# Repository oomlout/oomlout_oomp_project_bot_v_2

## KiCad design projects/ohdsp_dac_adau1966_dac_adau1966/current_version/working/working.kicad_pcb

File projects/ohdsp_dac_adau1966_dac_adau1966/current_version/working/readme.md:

# dac_adau1966
 
## summary 
* id: ohdsp_dac_adau1966_dac_adau1966
* user: ohdsp
* name: dac_adau1966
* board: dac_adau1966
* repo: https://github.com/ohdsp/DAC-ADAU1966
* src_file_repo_kicad_pcb: KiCad/DAC-ADAU1966.kicad_pcb
* src_file_repo_kicad_pcb_link: https://github.com/ohdsp/DAC-ADAU1966/tree/master/KiCad/DAC-ADAU1966.kicad_pcb

* src_file_repo_sch: 
* src_file_repo_sch_link: https://github.com/ohdsp/DAC-ADAU1966/tree/master/
* full details link: https://github.com/oomlout/oomlout_oomp_project_bot_v_2/tree/main/projects/ohdsp_dac_adau1966_dac_adau1966/current_version/working

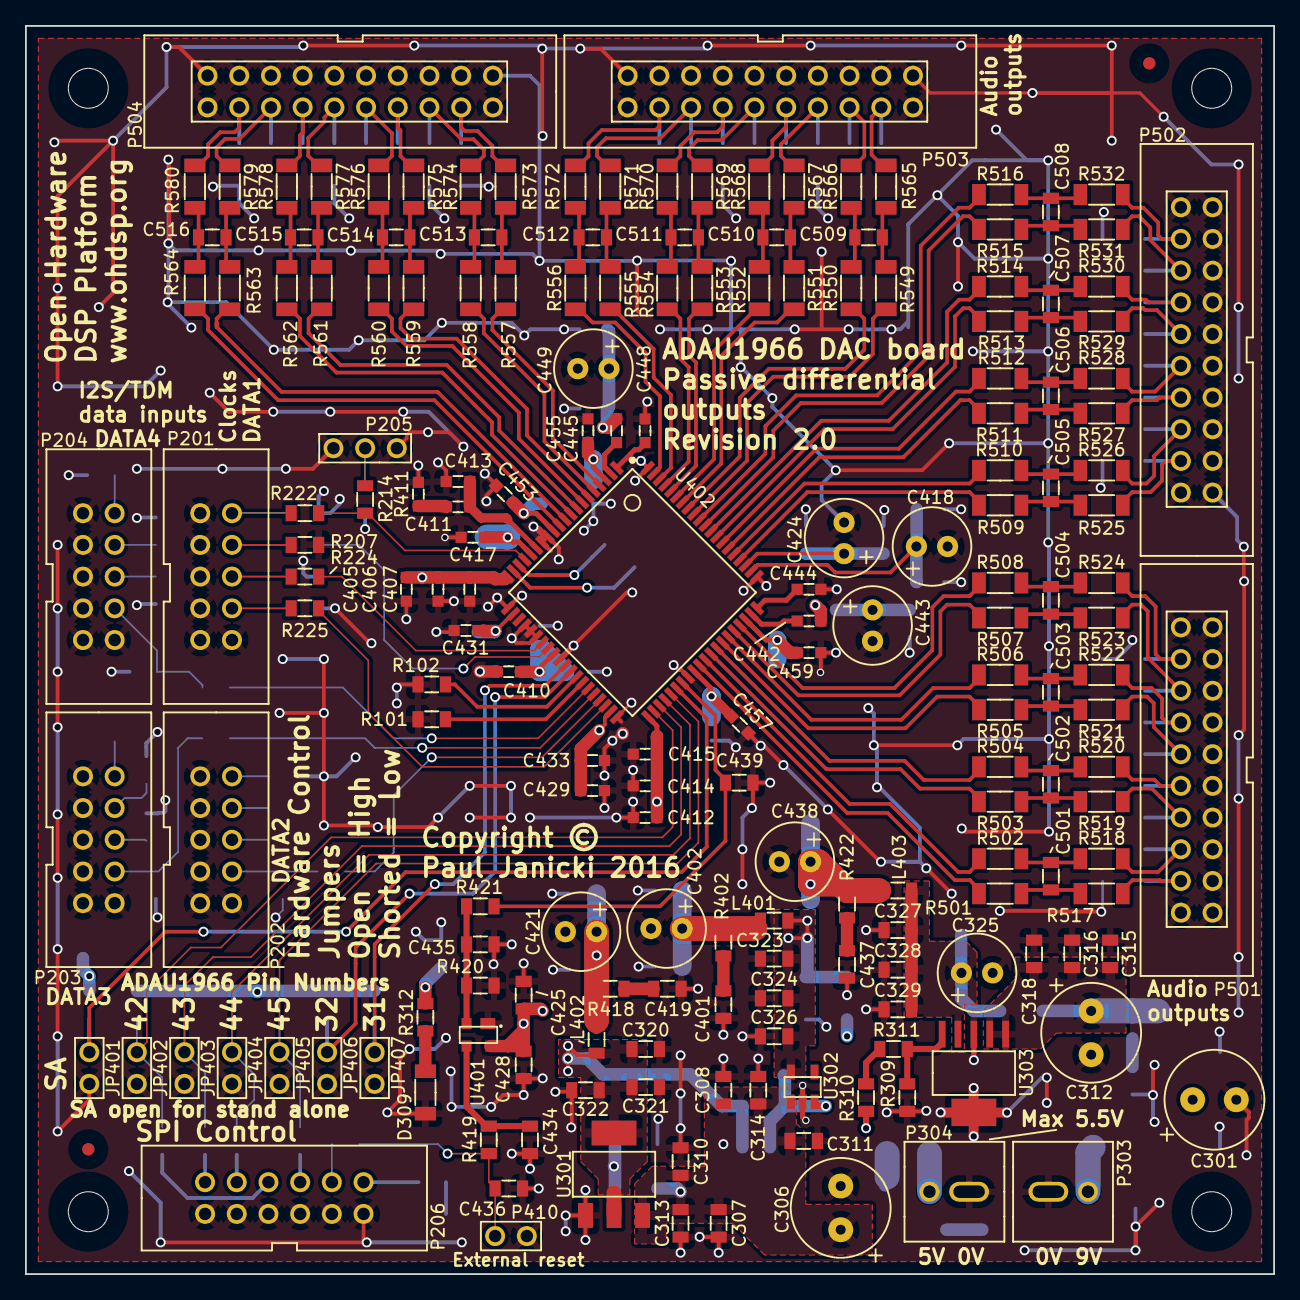
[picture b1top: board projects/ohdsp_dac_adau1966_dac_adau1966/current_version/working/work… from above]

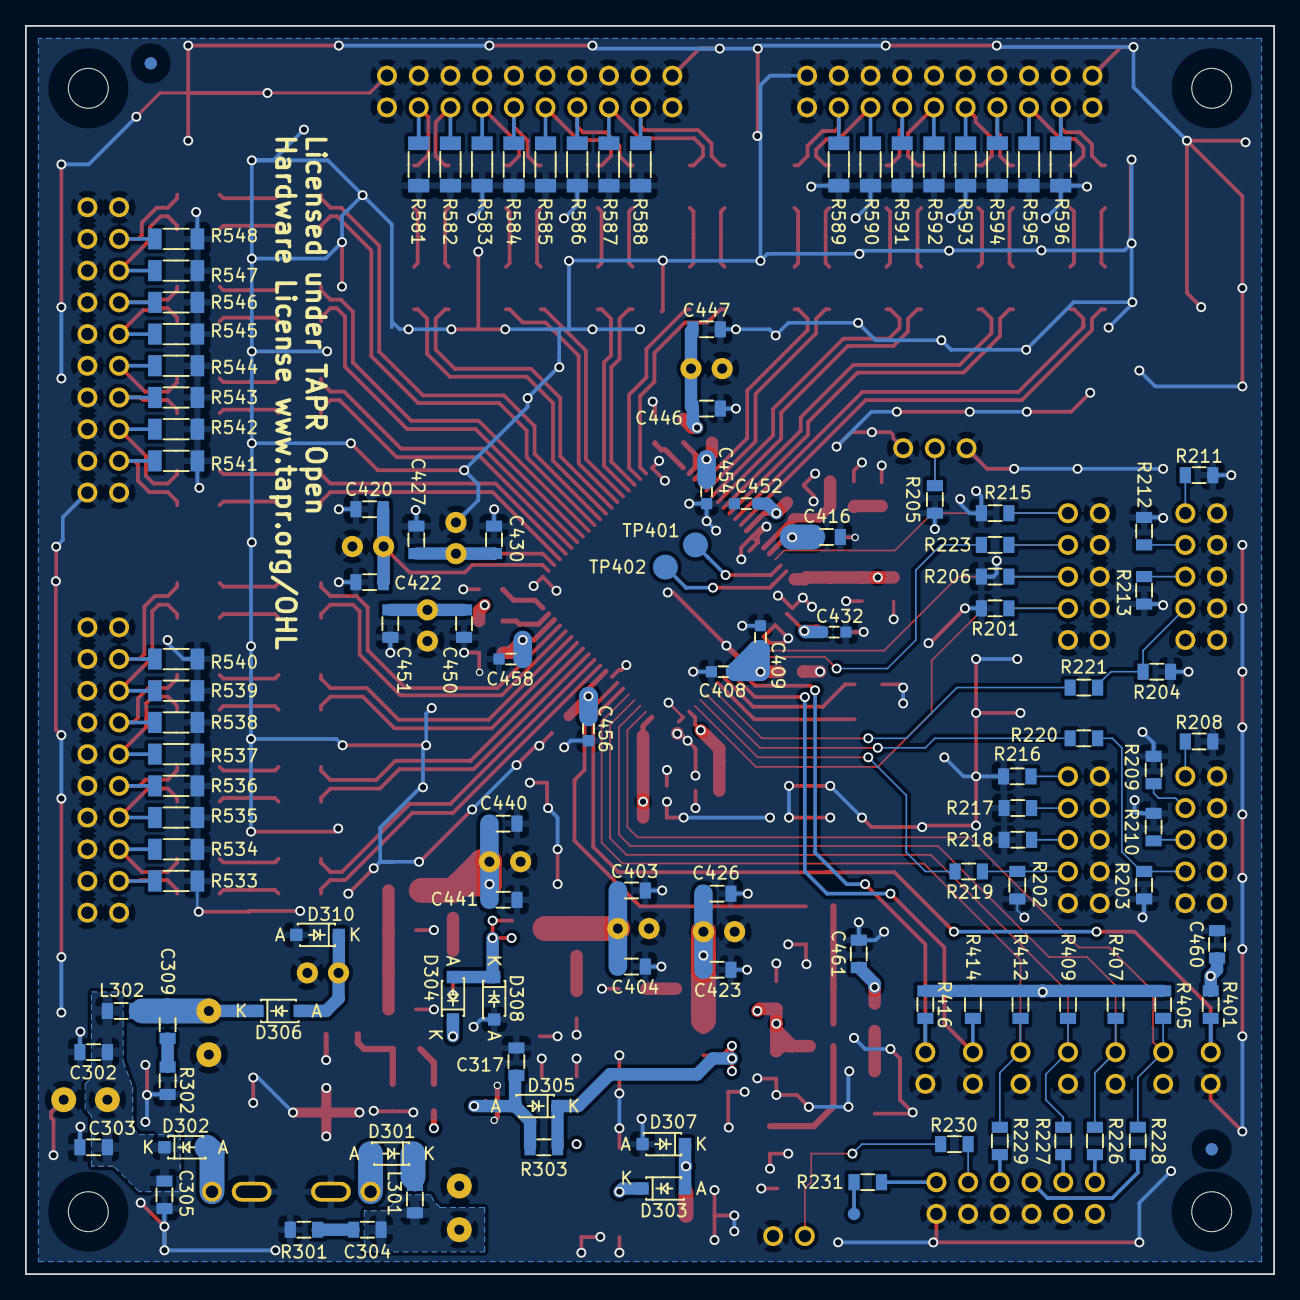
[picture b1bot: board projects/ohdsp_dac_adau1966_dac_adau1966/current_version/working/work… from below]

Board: 4 copper layers, 100.0 x 100.0 mm, 306 parts (114 on the bottom side), 172 nets.

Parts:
C301, C306, C312: 220u; CAP-TH-D8mmP3.5mm
C302, C307, C308, C315, C317, C320, C323, C327, C403, C416, C420, C423, C427, C440: 22u; SMD-0805
C303, C310, C311, C316, C321, C324, C328, C404, C422, C426, C428, C430, C434, C436, C439, C441, C446, C450, C460: 100n; SMD-0805
C304, C309, C401, C419, C437: 100p; SMD-0805
C305, C313, C314, C318, C322, C326, C329, C447, C451: 10n; SMD-0805
C325, C402, C418, C421, C424, C438: 220u; CAP-TH-D6.3mmP2.5mm
C405, C408, C412, C429, C432, C452, C454, C456, C458: 1u; SMD-0603
C406, C409, C414, C417, C431, C433, C453, C455, C457, C459: 100n; SMD-0603
C407, C410, C415: 10n; SMD-0603
C411: 5n6; SMD-0603
C413: 390p; SMD-0603
C425, C461: 10u; SMD-0805
C435: N/F; SMD-0805
C442, C444, C445, C448: 470n; SMD-0603
C443, C449: 47u; CAP-TH-D6.3mmP2.5mm
C501, C502, C503, C504, C505, C506, C507, C508, C509, C510, C511, C512, C513, C514, C515, C516: 2n7; SMD-0805
D301, D302, D303, D304, D306, D307, D308, D310: SS14L; DIODE-SOD-123
D305: B130LAW-7-F; DIODE-SOD-123
D309: Green LED 1206; SMD-1206
FID1, FID2, FID3, FID4: MNT_HOLE; FID-1MM-3MM
JP401, JP402, JP403, JP404, JP405, JP406, JP407: CONN_2x1; CONN_SIL_2_1MM
L301, L302, L401, L402, L403: 600R@100MHz; SMD-0805
MNT301, MNT302, MNT303, MNT304: MNT_HOLE; MNT_HOLE_3.2mm
P201, P202, P203, P204: CONN_02X05; CONN_DIL_2X5_BOX_1MM
P205: CONN_3x1; CONN_SIL_3_1MM
P206: CONN_02X06; CONN_DIL_2X6_BOX_1MM
P303, P304: CONN_2x1; CONN-2WAY-2.54mm-3.81mm-SPACING
P410: CONN_2x1; CONN_SIL_2_1MM
P501, P502, P503, P504: CONN_02X10; CONN_DIL_2X10_BOX_1MM
R101, R102, R419: 1k; SMD-0805
R201, R202, R203, R204, R205, R206, R207, R214, R215: N/F; SMD-0805
R208, R209, R210, R211, R212, R213, R216, R217, R218, R401, R405, R407, R409, R412, R414, R416: 10k; SMD-0805
R219, R220, R221, R222, R223, R224, R225, R227, R228, R229, R230, R231, R310: 0; SMD-0805
R226: 75; SMD-0805
R301, R302, R402, R418, R422: 47; SMD-0805
R303: 47k; SMD-0805
R309: 2k2; SMD-0805
R311: 6k8; SMD-0805
R312: 470; SMD-0805
R411: 562; SMD-0603
R420: 100k; SMD-0805
R421: 100; SMD-0805
R501, R502, R503, R504, R505, R506, R507, R508, R509, R510, R511, R512, R513, R514, R515, R516, R549, R550, R551, R552, R553, R554, R555, R556, R557, R558, R559, R560, R561, R562, R563, R564: 240; SMD-1206
R517, R518, R519, R520, R521, R522, R523, R524, R525, R526, R527, R528, R529, R530, R531, R532, R565, R566, R567, R568, R569, R570, R571, R572, R573, R574, R575, R576, R577, R578, R579, R580: 100; SMD-1206
R533, R534, R535, R536, R537, R538, R539, R540, R541, R542, R543, R544, R545, R546, R547, R548, R581, R582, R583, R584, R585, R586, R587, R588, R589, R590, R591, R592, R593, R594, R595, R596: 100k; SMD-1206
TP101: Test point; TP-1mm
TP401, TP402: Test point; TP-2mm
U301: TLV1117LV33DCY; IC-SOT-223
U302: TLV70025DDC; IC-SOT23-5
U303: TPS7A4501; IC-SOT223-6
U401: ADM811ZART; IC-SOT143
U402: IC-DAC-ADAU1966; IC-LQFP80-P065

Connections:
/ADAU1966/AVDD: C438.1, C440.1, C441.1, C442.1, C443.1, C445.1, C446.1, C447.1, C449.1, C450.1, C451.1, C452.1, C453.1, C454.1, C455.1, C456.1, C457.1, C458.1, C459.1, L403.2, R422.1, U402.3, U402.12, U402.49, U402.58
/ADAU1966/DACOUT_LRCLK: R223.2, U402.28
/ADAU1966/DACOUT_SDATA1: R225.2, U402.38
/ADAU1966/DACOUT_SDATA2: R219.2, U402.37
/ADAU1966/DACOUT_SDATA3: R220.2, U402.36
/ADAU1966/DACOUT_SDATA4: R221.2, U402.35
/ADAU1966/DACOUT_SDATA5: R101.1, U402.34
/ADAU1966/DACOUT_SDATA6: R102.1, U402.33
/ADAU1966/DAC_CLK: JP404.1, R227.1, R409.1, U402.44
/ADAU1966/DAC_CS: JP405.1, R229.1, R412.1, U402.45
/ADAU1966/DAC_MISO: JP403.1, R226.1, R407.1, U402.43
/ADAU1966/DAC_MOSI: JP402.1, R228.1, R405.1, U402.42
/ADAU1966/DAC_RESET: C439.1, R421.1, U402.47
/ADAU1966/DSDATA7: JP406.1, R414.1, U402.32
/ADAU1966/DSDATA8: JP407.1, R416.1, U402.31
/ADAU1966/DVDD: C402.1, C403.1, C404.1, C405.1, C406.1, C407.1, C408.1, C409.1, C410.1, C412.1, C414.1, C415.1, C416.1, C417.1, L401.2, R402.1, U402.16, U402.20, U402.29, U402.41
/ADAU1966/IOVDD: C421.1, C423.1, C426.1, C429.1, C431.1, C432.1, C433.1, L402.2, R418.1, U402.22, U402.39
/ADAU1966/LF: C411.1, C413.1, U402.15
/ADAU1966/MAN_RST_IN: C436.1, P410.1, R230.1, R419.2
/ADAU1966/MCLK: R214.2, R222.2, U402.17
/ADAU1966/OUT_1P: R501.1, U402.50
/ADAU1966/OUT_2P: R503.1, U402.52
/ADAU1966/OUT_3P: R505.1, U402.54
/ADAU1966/OUT_4P: R507.1, U402.56
/ADAU1966/OUT_5P: R509.1, U402.64
/ADAU1966/OUT_6P: R511.1, U402.66
/ADAU1966/OUT_7P: R513.1, U402.68
/ADAU1966/OUT_8P: R515.1, U402.70
/ADAU1966/OUT_9P: R549.1, U402.72
/ADAU1966/OUT_10P: R551.1, U402.74
/ADAU1966/OUT_11P: R553.1, U402.76
/ADAU1966/OUT_12P: R555.1, U402.78
/ADAU1966/OUT_13P: R557.1, U402.4
/ADAU1966/OUT_14P: R559.1, U402.6
/ADAU1966/OUT_15P: R561.1, U402.8
/ADAU1966/OUT_16P: R563.1, U402.10
/ADAU1966/SA: JP401.1, R401.1, U402.46
/AnaloguePassiveFilters/N1: R502.1, U402.51
/AnaloguePassiveFilters/N2: R504.1, U402.53
/AnaloguePassiveFilters/N3: R506.1, U402.55
/AnaloguePassiveFilters/N4: R508.1, U402.57
/AnaloguePassiveFilters/N5: R510.1, U402.65
/AnaloguePassiveFilters/N6: R512.1, U402.67
/AnaloguePassiveFilters/N7: R514.1, U402.69
/AnaloguePassiveFilters/N8: R516.1, U402.71
/AnaloguePassiveFilters/N9: R550.1, U402.73
/AnaloguePassiveFilters/N10: R552.1, U402.75
/AnaloguePassiveFilters/N11: R554.1, U402.77
/AnaloguePassiveFilters/N12: R556.1, U402.79
/AnaloguePassiveFilters/N13: R558.1, U402.5
/AnaloguePassiveFilters/N14: R560.1, U402.7
/AnaloguePassiveFilters/N15: R562.1, U402.9
/AnaloguePassiveFilters/N16: R564.1, U402.11
/Connectors/BCLK: R224.2, U402.27
/Connectors/GPIO: R231.1, TP101.1
GNDA: C301.2, C302.2, C303.2, C305.2, C306.2, C307.2, C308.2, C310.2, C311.2, C312.2, C313.2, C314.2, C315.2, C316.2, C317.2, C318.2, C320.2, C321.2, C322.2, C323.2, C324.2, C325.2, C326.2, C327.2, C328.2, C329.2, C401.2, C402.2, C403.2, C404.2, C405.2, C406.2, C407.2, C408.2, C409.2, C410.2, C412.2, C413.2, C414.2, C415.2, C416.2, C417.2, C418.2, C419.2, C420.2, C421.2, C422.2, C423.2, C424.2, C425.2, C426.2, C427.2, C428.2, C429.2, C430.2, C431.2, C432.2, C433.2, C434.2, C435.2, C436.2, C437.2, C438.2, C439.2, C440.2, C441.2, C443.2, C444.2, C446.2, C447.2, C448.2, C449.2, C450.2, C451.2, C452.2, C453.2, C454.2, C455.2, C456.2, C457.2, C458.2, C459.2, C460.2, C461.2, D307.1, D308.1, D309.2, D310.1, JP401.2, JP402.2, JP403.2, JP404.2, JP405.2, JP406.2, JP407.2, P201.1, P201.3, P201.5, P201.7, P201.9, P201.10, P202.1, P202.3, P202.5, P202.7, P202.9, P202.10, P203.1, P203.3, P203.5, P203.7, P203.9, P203.10, P204.1, P204.3, P204.5, P204.7, P204.9, P204.10, P205.1, P205.3, P206.1, P206.3, P206.5, P206.7, P206.9, P206.11, P303.2, P304.2, P410.2, P501.1, P501.2, P501.3, P501.5, P501.7, P501.9, P501.11, P501.13, P501.15, P501.17, P501.19, P501.20, P502.1, P502.2, P502.3, P502.5, P502.7, P502.9, P502.11, P502.13, P502.15, P502.17, P502.19, P502.20, P503.1, P503.2, P503.3, P503.5, P503.7, P503.9, P503.11, P503.13, P503.15, P503.17, P503.19, P503.20, P504.1, P504.2, P504.3, P504.5, P504.7, P504.9, P504.11, P504.13, P504.15, P504.17, P504.19, P504.20, R101.2, R102.2, R201.1, R202.1, R203.1, R204.1, R205.1, R206.1, R207.1, R208.2, R209.2, R210.2, R211.2, R212.2, R213.2, R215.1, R216.2, R217.2, R218.2, R301.2, R302.2, R309.2, R411.2, R420.1, R533.2, R534.2, R535.2, R536.2, R537.2, R538.2, R539.2, R540.2, R541.2, R542.2, R543.2, R544.2, R545.2, R546.2, R547.2, R548.2, R581.2, R582.2, R583.2, R584.2, R585.2, R586.2, R587.2, R588.2, R589.2, R590.2, R591.2, R592.2, R593.2, R594.2, R595.2, R596.2, U301.1, U302.2, U303.3, U401.1, U402.13, U402.14, U402.21, U402.24, U402.25, U402.26, U402.30, U402.40, U402.48, U402.61, U402.80
unnamed: C301.1, C302.1, C303.1, C305.1, D302.2, L302.1
unnamed: C304.1, C306.1, C307.1, C308.1, C310.1, C311.1, C313.1, C314.1, D303.2, D304.2, L301.2, U301.3, U302.1
unnamed: C304.2, R301.1
unnamed: C309.1, C312.1, C315.1, C316.1, C318.1, D306.2, L302.2, U303.1, U303.2
unnamed: C309.2, R302.1
unnamed: C317.1, D305.1, R303.2, U302.3
unnamed: C401.1, R402.2
unnamed: C411.2, R411.1
unnamed: C418.1, C420.1, C422.1, U402.62
unnamed: C419.1, R418.2
unnamed: C424.1, C427.1, C430.1, U402.63
unnamed: C434.1, R419.1, U401.3
unnamed: C435.1, R420.2, R421.2, U401.2
unnamed: C437.1, R422.2
unnamed: C442.2, U402.59
unnamed: C444.1, U402.60
unnamed: C445.2, U402.2
unnamed: C448.1, U402.1
unnamed: C501.1, R502.2, R518.1
unnamed: C501.2, R501.2, R517.1
unnamed: C502.1, R504.2, R520.1
unnamed: C502.2, R503.2, R519.1
unnamed: C503.1, R506.2, R522.1
unnamed: C503.2, R505.2, R521.1
unnamed: C504.1, R508.2, R524.1
unnamed: C504.2, R507.2, R523.1
unnamed: C505.1, R510.2, R526.1
unnamed: C505.2, R509.2, R525.1
unnamed: C506.1, R512.2, R528.1
unnamed: C506.2, R511.2, R527.1
unnamed: C507.1, R514.2, R530.1
unnamed: C507.2, R513.2, R529.1
unnamed: C508.1, R516.2, R532.1
unnamed: C508.2, R515.2, R531.1
unnamed: C509.1, R550.2, R566.1
unnamed: C509.2, R549.2, R565.1
unnamed: C510.1, R552.2, R568.1
unnamed: C510.2, R551.2, R567.1
unnamed: C511.1, R554.2, R570.1
unnamed: C511.2, R553.2, R569.1
unnamed: C512.1, R556.2, R572.1
unnamed: C512.2, R555.2, R571.1
unnamed: C513.1, R558.2, R574.1
unnamed: C513.2, R557.2, R573.1
unnamed: C514.1, R560.2, R576.1
unnamed: C514.2, R559.2, R575.1
unnamed: C515.1, R562.2, R578.1
unnamed: C515.2, R561.2, R577.1
unnamed: C516.1, R564.2, R580.1
unnamed: C516.2, R563.2, R579.1
unnamed: D301.1, P304.1
unnamed: D301.2, L301.1
unnamed: D302.1, P303.1
unnamed: D309.1, R312.2
unnamed: P201.2, R215.2, R222.1
unnamed: P201.4, R207.2, R223.1
unnamed: P201.6, R206.2, R224.1
unnamed: P201.8, R201.2, R225.1
unnamed: P202.2, R216.1
unnamed: P202.4, R217.1
unnamed: P202.6, R218.1
unnamed: P202.8, R202.2, R219.1
unnamed: P203.2, R208.1
unnamed: P203.4, R209.1
unnamed: P203.6, R210.1
unnamed: P203.8, R203.2, R220.1
unnamed: P204.2, R211.1
unnamed: P204.4, R212.1
unnamed: P204.6, R213.1
unnamed: P204.8, R204.2, R221.1
unnamed: P205.2, R205.2, R214.1
unnamed: P206.2, R226.2
unnamed: P206.4, R227.2
unnamed: P206.6, R228.2
unnamed: P206.8, R229.2
unnamed: P206.10, R230.2
unnamed: P206.12, R231.2
unnamed: P501.4, R517.2, R533.1
unnamed: P501.6, R518.2, R534.1
unnamed: P501.8, R519.2, R535.1
unnamed: P501.10, R520.2, R536.1
unnamed: P501.12, R521.2, R537.1
unnamed: P501.14, R522.2, R538.1
unnamed: P501.16, R523.2, R539.1
unnamed: P501.18, R524.2, R540.1
unnamed: P502.4, R525.2, R541.1
unnamed: P502.6, R526.2, R542.1
unnamed: P502.8, R527.2, R543.1
unnamed: P502.10, R528.2, R544.1
unnamed: P502.12, R529.2, R545.1
unnamed: P502.14, R530.2, R546.1
unnamed: P502.16, R531.2, R547.1
unnamed: P502.18, R532.2, R548.1
unnamed: P503.4, R565.2, R581.1
unnamed: P503.6, R566.2, R582.1
unnamed: P503.8, R567.2, R583.1
unnamed: P503.10, R568.2, R584.1
unnamed: P503.12, R569.2, R585.1
unnamed: P503.14, R570.2, R586.1
unnamed: P503.16, R571.2, R587.1
unnamed: P503.18, R572.2, R588.1
unnamed: P504.4, R573.2, R589.1
unnamed: P504.6, R574.2, R590.1
unnamed: P504.8, R575.2, R591.1
unnamed: P504.10, R576.2, R592.1
unnamed: P504.12, R577.2, R593.1
unnamed: P504.14, R578.2, R594.1
unnamed: P504.16, R579.2, R595.1
unnamed: P504.18, R580.2, R596.1
unnamed: R309.1, R311.2, U303.5
unnamed: R310.1, R311.1
unnamed: TP401.1, U402.18
unnamed: TP402.1, U402.19
VAA: C325.1, C327.1, C328.1, C329.1, D306.1, D310.2, L403.1, R310.2, U303.4
VDD: C323.1, C324.1, C326.1, C425.1, C428.1, D304.1, D308.2, L401.1, U302.5, U401.4
VPP: C320.1, C321.1, C322.1, C460.1, C461.1, D303.1, D305.2, D307.2, L402.1, R303.1, R312.1, R401.2, R405.2, R407.2, R409.2, R412.2, R414.2, R416.2, U301.2

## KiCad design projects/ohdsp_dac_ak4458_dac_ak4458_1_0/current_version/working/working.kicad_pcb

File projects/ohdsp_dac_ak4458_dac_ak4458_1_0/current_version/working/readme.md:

# dac_ak4458
 
## summary 
* id: ohdsp_dac_ak4458_dac_ak4458_1_0
* user: ohdsp
* name: dac_ak4458
* board: dac_ak4458_1_0
* repo: https://github.com/ohdsp/DAC-AK4458
* src_file_repo_kicad_pcb: KiCad/DAC-AK4458-1.0.kicad_pcb
* src_file_repo_kicad_pcb_link: https://github.com/ohdsp/DAC-AK4458/tree/master/KiCad/DAC-AK4458-1.0.kicad_pcb

* src_file_repo_sch: 
* src_file_repo_sch_link: https://github.com/ohdsp/DAC-AK4458/tree/master/
* full details link: https://github.com/oomlout/oomlout_oomp_project_bot_v_2/tree/main/projects/ohdsp_dac_ak4458_dac_ak4458_1_0/current_version/working

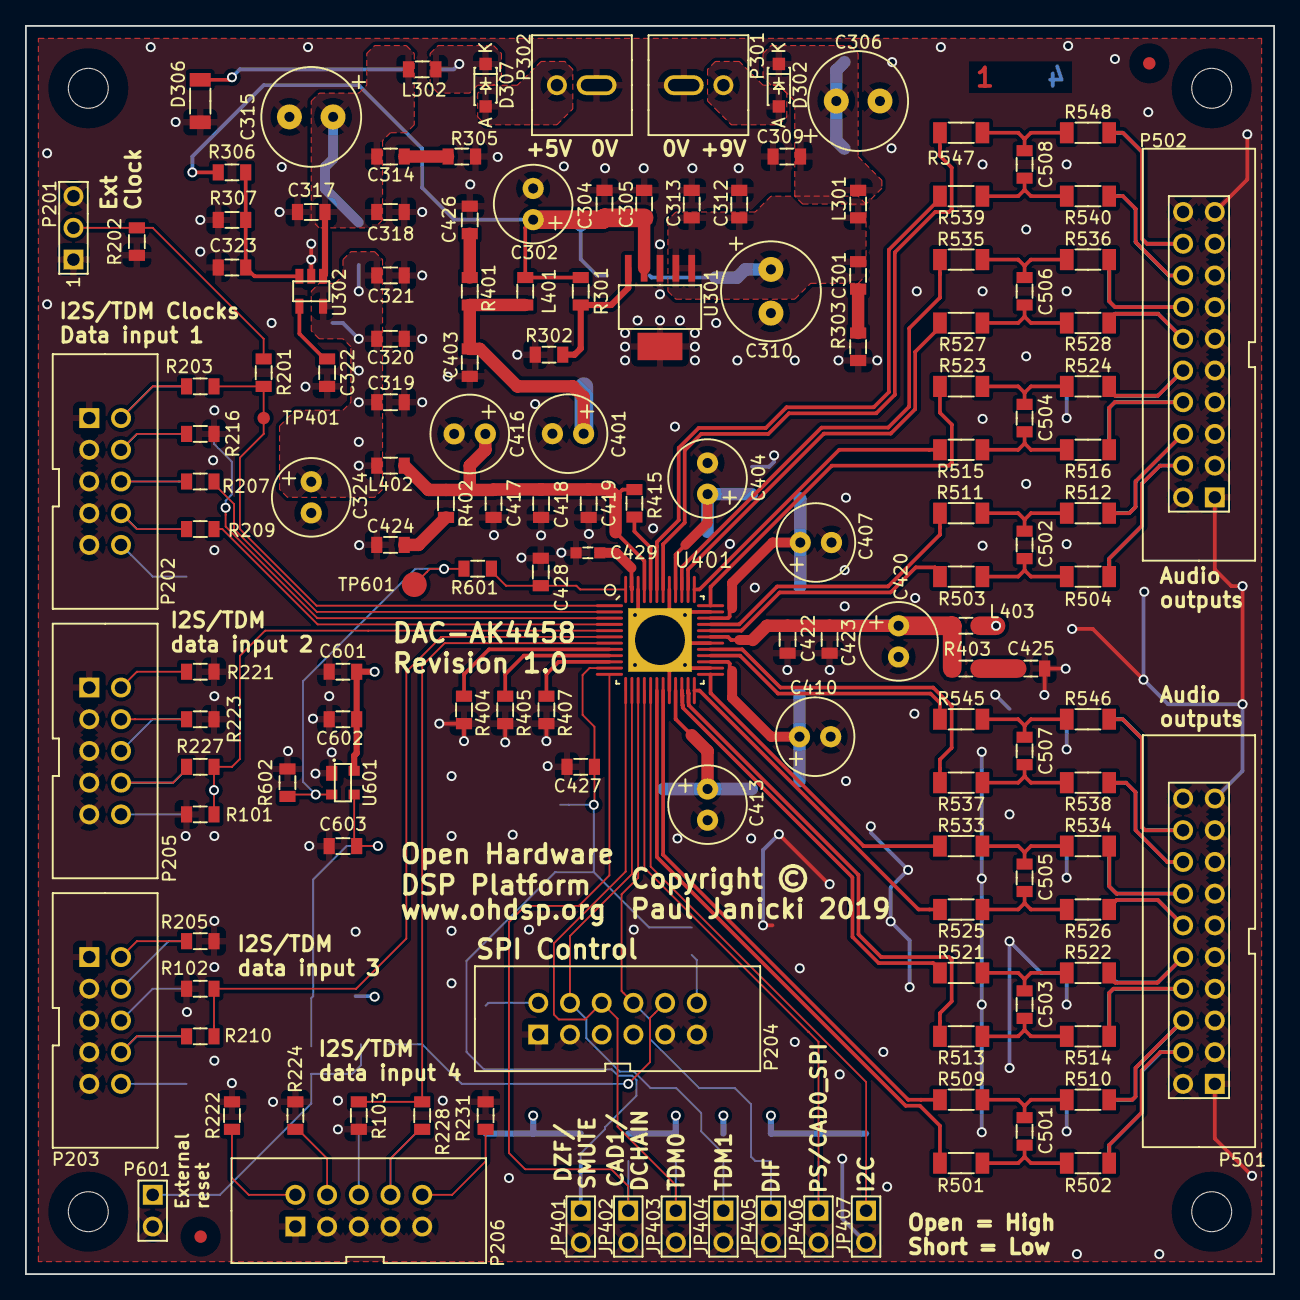
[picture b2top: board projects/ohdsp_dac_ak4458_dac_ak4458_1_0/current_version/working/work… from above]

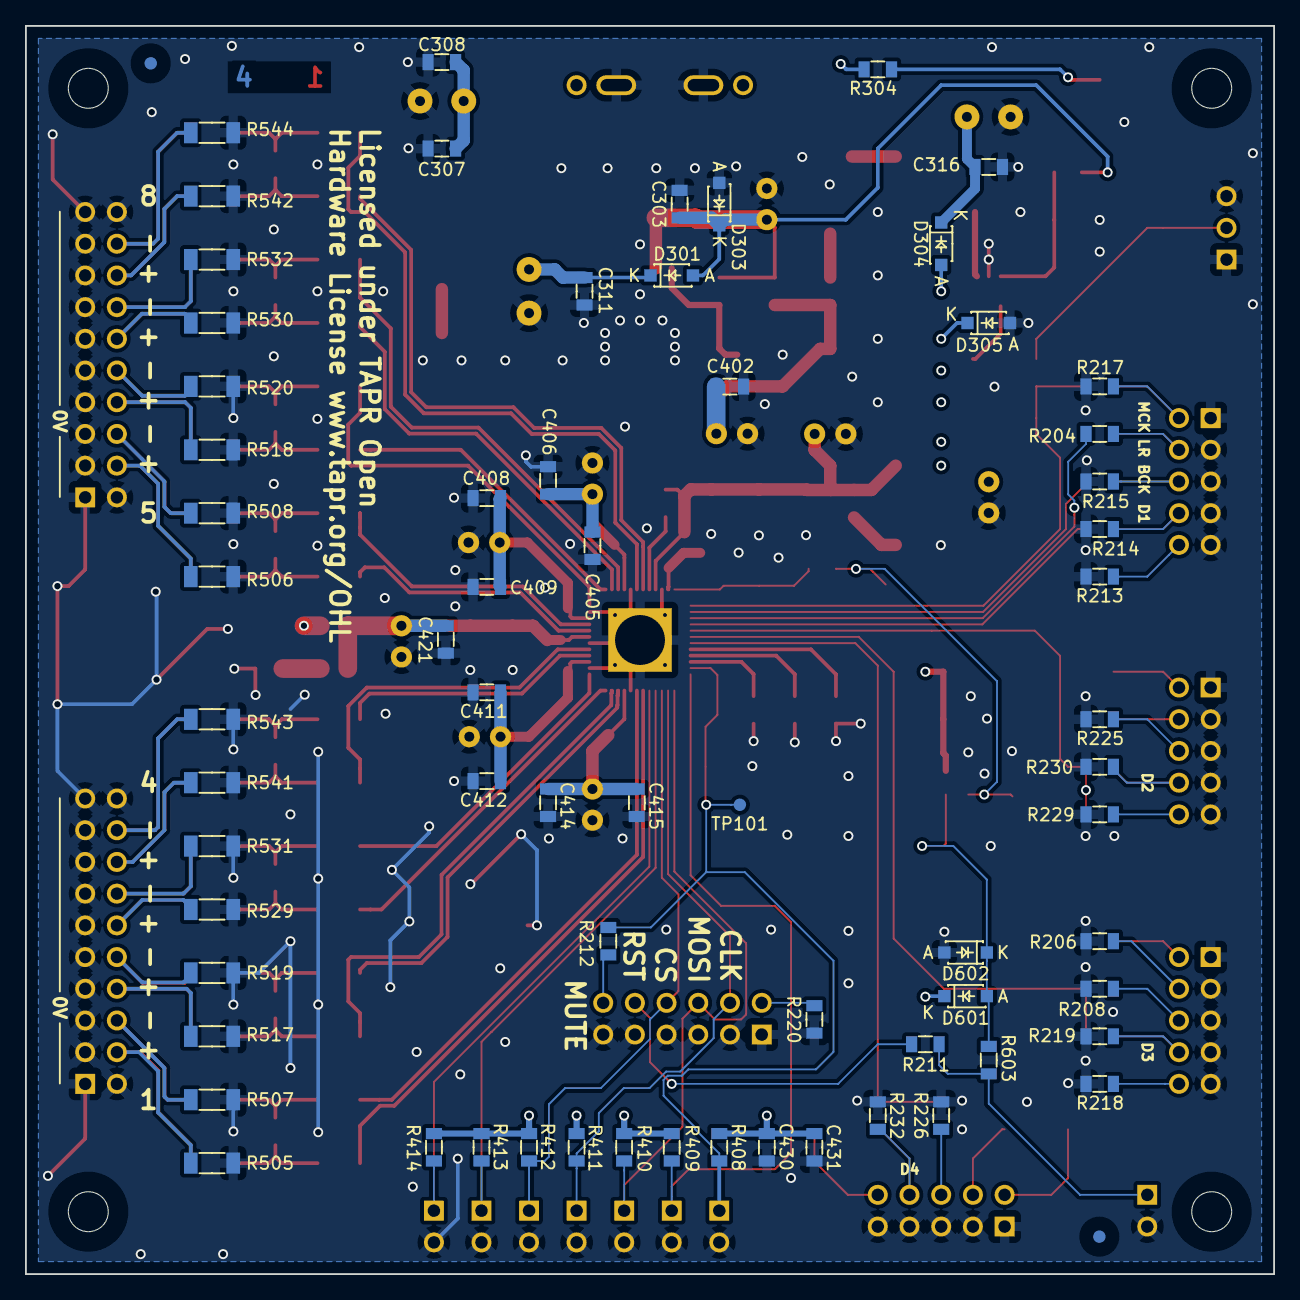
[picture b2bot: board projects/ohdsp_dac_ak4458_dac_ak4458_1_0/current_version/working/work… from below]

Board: 4 copper layers, 100.0 x 100.0 mm, 220 parts (68 on the bottom side), 116 nets.

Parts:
C301, C314, C424, C425, C426: 100p; SMD-0805
C302, C324, C401, C416, C420: 220u; CAP-TH-D6.3mmP2.5mm
C303, C307, C311, C316, C319, C402, C417, C421: 22u; SMD-0805
C304, C308, C312, C317, C320, C323, C403, C405, C408, C411, C414, C418, C422, C428, C430, C602: 100n; SMD-0805
C305, C309, C313, C318, C321, C406, C409, C412, C415, C419, C423, C427, C603: 10n; SMD-0805
C306, C310, C315: 220u; CAP-TH-D8mmP3.5mm
C322: N/F; SMD-0805
C404, C407, C410, C413: 47u; CAP-TH-D6.3mmP2.5mm
C429: 1u; SMD-0603
C431, C601: 10u; SMD-0805
C501, C502, C503, C504, C505, C506, C507, C508: 2n7; SMD-0805
D301, D302, D303, D304, D305, D307, D601, D602: 1N5819HW; DIODE-SOD-123
D306: Green LED 1206; SMD-1206
FID301, FID302, FID303, FID304: MNT_HOLE; FID-1MM-3MM
JP401, JP402, JP403, JP404, JP405, JP406, JP407: CONN_2x1; CONN_SIL_2_1MM
L301, L302, L401, L402, L403: 600R@100MHz; SMD-0805
MNT301, MNT302, MNT303, MNT304: MNT_HOLE; MNT_HOLE_3.2mm
P201: CONN_3x1; CONN_SIL_3_1MM
P202, P203, P205, P206: CONN_02X05; CONN_DIL_2X5_BOX_1MM
P204: CONN_02X06; CONN_DIL_2X6_BOX_1MM
P301, P302: CONN_2x1; CONN-2WAY-2.54mm-3.81mm-SPACING
P501, P502: CONN_02X10; CONN_DIL_2X10_BOX_1MM
P601: CONN_2x1; CONN_SIL_2_1MM
R101, R102, R103, R213, R218, R220, R229, R231, R304, R603: 1k; SMD-0805
R201, R202, R214, R215, R216, R217, R219, R230, R232: N/F; SMD-0805
R203, R204, R207, R209, R210, R211, R212, R227, R228, R404, R405, R407, R415: 0; SMD-0805
R205, R206, R208, R221, R222, R223, R224, R225, R226, R408, R409, R410, R411, R412, R413, R414: 10k; SMD-0805
R301: 6k8; SMD-0805
R302: 2k2; SMD-0805
R303, R305, R401, R402, R403: 47; SMD-0805
R306: 10K; SMD-0805
R307: 220K; SMD-0805
R501, R503, R509, R511, R513, R515, R521, R523, R525, R527, R533, R535, R537, R539, R545, R547: 240; SMD-1206
R502, R504, R510, R512, R514, R516, R522, R524, R526, R528, R534, R536, R538, R540, R546, R548: 100; SMD-1206
R505, R506, R507, R508, R517, R518, R519, R520, R529, R530, R531, R532, R541, R542, R543, R544: 100k; SMD-1206
R601: 100; SMD-0805
R602: 100k; SMD-0805
TP101, TP401: Test point; TP-1mm
TP601: PIN; TP-2mm
U301: TPS7A4501DCQ; IC-SOT223-6
U302: TLV70033DDC; IC-SOT23-5
U401: AK4458VN; IC_QFN_48_5.1mmpad_HF_HS
U601: CAT811TTBI; IC-SOT143

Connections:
+3V3: C319.1, C320.1, C321.1, C324.1, C430.1, C431.1, C601.1, C602.1, D304.1, D305.2, D601.2, L402.1, R408.2, R409.2, R410.2, R411.2, R412.2, R413.2, R414.2, U302.5, U601.4
+5VA: C302.1, C303.1, C304.1, C305.1, D301.1, D303.2, L401.1, L403.1, R301.1, R306.2, U301.4
/AK4458/AVDD: C420.1, C421.1, C422.1, C423.1, L403.2, R403.1, U401.31
/AK4458/CAD1/DCHAIN: JP402.1, R409.1, U401.12
/AK4458/I2C: JP407.1, R414.1, U401.17
/AK4458/OUT_1P: R501.1, U401.18
/AK4458/OUT_2P: R513.1, U401.23
/AK4458/OUT_3P: R525.1, U401.24
/AK4458/OUT_4P: R537.1, U401.29
/AK4458/OUT_5P: R503.1, U401.32
/AK4458/OUT_6P: R515.1, U401.37
/AK4458/OUT_7P: R527.1, U401.38
/AK4458/OUT_8P: R539.1, U401.43
/AK4458/PS/CAD0_SPI: JP406.1, R413.1, U401.16
/AK4458/TVDD: C416.1, C417.1, C418.1, C419.1, L402.2, R402.1, R415.2, U401.45
/AK4458/VREF: C401.1, C402.1, C403.1, C404.1, C405.1, C406.1, C407.1, C408.1, C409.1, C410.1, C411.1, C412.1, C413.1, C414.1, C415.1, L401.2, R401.1, U401.21, U401.27, U401.34, U401.40
/AnaloguePassiveFilters/N1: R509.1, U401.19
/AnaloguePassiveFilters/N2: R521.1, U401.22
/AnaloguePassiveFilters/N3: R533.1, U401.25
/AnaloguePassiveFilters/N4: R545.1, U401.28
/AnaloguePassiveFilters/N5: R511.1, U401.33
/AnaloguePassiveFilters/N6: R523.1, U401.36
/AnaloguePassiveFilters/N7: R535.1, U401.39
/AnaloguePassiveFilters/N8: R547.1, U401.42
/BCLK: R207.2, U401.2
/GLB_RST: C428.1, R601.1, U401.48
/LRCLK: R204.2, U401.3
/MCLK: R201.2, R203.2, TP401.1, U401.1
/MUTE: C427.1, JP401.1, R212.1, R408.1, TP101.1, U401.11
/Reset-CAT811/RST_IN: P601.1, R211.1, R603.2
/SDATA1: R209.2, U401.4
/SDATA2: R101.1, R227.2, U401.5
/SDATA3: R102.1, R210.2, U401.6
/SDATA4: R103.1, R228.2, U401.7
/SPI_CLK: JP404.1, P204.4, R411.1, U401.14
/SPI_CS: JP405.1, P204.8, R412.1, U401.15
/SPI_MOSI: JP403.1, P204.6, R410.1, U401.13
GNDA: C302.2, C303.2, C304.2, C305.2, C306.2, C307.2, C308.2, C309.2, C310.2, C311.2, C312.2, C313.2, C315.2, C316.2, C317.2, C318.2, C319.2, C320.2, C321.2, C322.2, C323.2, C324.2, C401.2, C402.2, C403.2, C404.2, C405.2, C406.2, C407.2, C408.2, C409.2, C410.2, C411.2, C412.2, C413.2, C414.2, C415.2, C416.2, C417.2, C418.2, C419.2, C420.2, C421.2, C422.2, C423.2, C424.2, C425.2, C426.2, C427.2, C428.2, C429.2, C430.2, C431.2, C601.2, C602.2, C603.2, D303.1, D305.1, D306.2, D602.1, JP401.2, JP402.2, JP403.2, JP404.2, JP405.2, JP406.2, JP407.2, P201.1, P201.3, P202.1, P202.3, P202.5, P202.7, P202.9, P203.1, P203.3, P203.5, P203.7, P203.9, P204.1, P204.3, P204.5, P204.7, P204.9, P204.11, P205.1, P205.3, P205.5, P205.7, P205.9, P206.1, P206.3, P206.5, P206.7, P206.9, P301.2, P302.2, P501.1, P501.2, P501.3, P501.5, P501.7, P501.9, P501.11, P501.13, P501.15, P501.17, P501.19, P501.20, P502.1, P502.2, P502.3, P502.5, P502.7, P502.9, P502.11, P502.13, P502.15, P502.17, P502.19, P502.20, P601.2, R101.2, R102.2, R103.2, R202.1, R205.2, R206.2, R208.2, R213.1, R214.1, R215.1, R216.1, R217.1, R218.1, R219.1, R220.1, R221.2, R222.2, R223.2, R224.2, R225.2, R226.2, R229.1, R230.1, R231.1, R232.1, R302.2, R303.2, R305.2, R307.2, R404.2, R405.2, R407.2, R505.2, R506.2, R507.2, R508.2, R517.2, R518.2, R519.2, R520.2, R529.2, R530.2, R531.2, R532.2, R541.2, R542.2, R543.2, R544.2, R602.2, U301.3, U302.2, U401.20, U401.26, U401.30, U401.35, U401.41, U401.46, U401.EP, U601.1
unnamed: C301.1, C310.1, C311.1, C312.1, C313.1, D301.2, L301.2, U301.1, U301.2
unnamed: C301.2, R303.1
unnamed: C306.1, C307.1, C308.1, C309.1, D302.2, L301.1
unnamed: C314.1, C315.1, C316.1, C317.1, C318.1, D304.2, L302.2, U302.1
unnamed: C314.2, R305.1
unnamed: C322.1, U302.4
unnamed: C323.1, R306.1, R307.1, U302.3
unnamed: C424.1, R402.2
unnamed: C425.1, R403.2
unnamed: C426.1, R401.2
unnamed: C429.1, U401.47
unnamed: C501.1, R509.2, R510.1
unnamed: C501.2, R501.2, R502.1
unnamed: C502.1, R511.2, R512.1
unnamed: C502.2, R503.2, R504.1
unnamed: C503.1, R521.2, R522.1
unnamed: C503.2, R513.2, R514.1
unnamed: C504.1, R523.2, R524.1
unnamed: C504.2, R515.2, R516.1
unnamed: C505.1, R533.2, R534.1
unnamed: C505.2, R525.2, R526.1
unnamed: C506.1, R535.2, R536.1
unnamed: C506.2, R527.2, R528.1
unnamed: C507.1, R545.2, R546.1
unnamed: C507.2, R537.2, R538.1
unnamed: C508.1, R547.2, R548.1
unnamed: C508.2, R539.2, R540.1
unnamed: C603.1, D601.1, D602.2, R603.1, U601.3
unnamed: D302.1, P301.1
unnamed: D306.1, R304.2
unnamed: D307.1, P302.1
unnamed: P201.2, R201.1, R202.2
unnamed: P202.2, R203.1, R217.2
unnamed: P202.4, R204.1, R216.2
unnamed: P202.6, R207.1, R215.2
unnamed: P202.8, R209.1, R214.2
unnamed: P202.10, R213.2
unnamed: P203.2, R205.1
unnamed: P203.4, R206.1
unnamed: P203.6, R208.1
unnamed: P203.8, R210.1, R219.2
unnamed: P203.10, R218.2
unnamed: P204.2, R220.2
unnamed: P204.10, R211.2
unnamed: P204.12, R212.2
unnamed: P205.2, R221.1
unnamed: P205.4, R223.1
unnamed: P205.6, R225.1
unnamed: P205.8, R227.1, R230.2
unnamed: P205.10, R229.2
unnamed: P206.2, R222.1
unnamed: P206.4, R224.1
unnamed: P206.6, R226.1
unnamed: P206.8, R228.1, R232.2
unnamed: P206.10, R231.2
unnamed: P501.4, R502.2, R505.1
unnamed: P501.6, R507.1, R510.2
unnamed: P501.8, R514.2, R517.1
unnamed: P501.10, R519.1, R522.2
unnamed: P501.12, R526.2, R529.1
unnamed: P501.14, R531.1, R534.2
unnamed: P501.16, R538.2, R541.1
unnamed: P501.18, R543.1, R546.2
unnamed: P502.4, R504.2, R506.1
unnamed: P502.6, R508.1, R512.2
unnamed: P502.8, R516.2, R518.1
unnamed: P502.10, R520.1, R524.2
unnamed: P502.12, R528.2, R530.1
unnamed: P502.14, R532.1, R536.2
unnamed: P502.16, R540.2, R542.1
unnamed: P502.18, R544.1, R548.2
unnamed: R301.2, R302.1, U301.5
unnamed: R404.1, U401.8
unnamed: R405.1, U401.9
unnamed: R407.1, U401.10
unnamed: R415.1, U401.44
unnamed: R601.2, R602.1, TP601.1, U601.2
VCC: D307.2, L302.1, R304.1

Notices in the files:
projects/ohdsp_dac_adau1966_dac_adau1966/current_version/working/working.kicad_pcb:
Licensed under the TAPR Open Hardware License (www.tapr.org/OHL). This documentation
Copyright Paul Janicki 2016
Licensed under TAPR Open
Copyright ©
projects/ohdsp_dac_ak4458_dac_ak4458_1_0/current_version/working/working.kicad_pcb:
Copyright Paul Janicki 2019
projects/ohdsp_psu_5v_6v_dual9v_psu_5v_6v_dual9v/current_version/working/working.kicad_pcb:
Licensed under TAPR Open Hardware License
Copyright © Paul Janicki 2016
